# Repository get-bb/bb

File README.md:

<p align="center">
  <picture>
    <source media="(prefers-color-scheme: dark)" srcset="https://github.com/user-attachments/assets/e40bda56-54a4-47f8-a417-6bbadf2e5b40">
    <source media="(prefers-color-scheme: light)" srcset="https://github.com/user-attachments/assets/4d9d02fb-c179-449b-a38a-041955143232">
    
  </picture>
</p>

# bb

bb is an agentic IDE that builds itself. It can control, customize, and automate
itself, laying the groundwork for your own software factory.

Every surface — the desktop app, web app, CLI, and HTTP API — is a first-class
way to drive bb. Work runs in threads you can follow live, steer at any point,
or hand off to another agent.

> [!NOTE]
> bb is in active development. Core architecture is stable, but workflows
> and surfaces are still evolving.

## Use bb

### Download the desktop app

The recommended way to start using bb is the desktop app:

**[Download the latest desktop app](https://github.com/get-bb/bb/releases/tag/desktop-latest)**

The desktop app supports macOS on Apple Silicon (arm64). The Linux x64 AppImage
and the Windows x64 installer are alpha: expect problems, and please report
them. Intel Mac users should run bb with `npx` instead. Native Windows needs
[Git for Windows](https://git-scm.com/download/win), which bb uses for Git and
for environment setup scripts. You can also run bb inside
[WSL2 (Windows Subsystem for Linux)](https://learn.microsoft.com/windows/wsl/install):
install WSL2 first, then run the `npx` command below from your WSL2 (Linux)
shell.

Early adopters can install
**[bb Nightly](https://github.com/get-bb/bb/releases/tag/desktop-nightly)**
alongside the stable desktop app. It has a separate application identity,
yellow icon, and auto-update feed.

### Or run it anywhere with npx

```bash
npx bb-app@latest
```

Then open `http://localhost:38886`.

To control bb from outside bb with the `bb` CLI, open **Settings → General →
Command line** and choose **Install**. See
[The bb Command On PATH](./docs/configuration.md#the-bb-command-on-path).

To run the newest automated build instead:

```bash
npx bb-app@nightly
```

npm 12 and later block dependency install scripts by default. bb needs those
scripts to build its native add-ons. If your npm version is 12 or later, allow
the scripts for the install:

```bash
npx --allow-scripts=better-sqlite3,node-pty,@parcel/watcher bb-app@latest
```

Or set the policy once for all global installs:

```bash
npm config set allow-scripts=better-sqlite3,node-pty,@parcel/watcher --location=user
```

bb uses the provider CLI you already have authenticated.

For install requirements, provider setup, configuration, and package-focused
docs, start with
[`packages/bb-app`](./packages/bb-app/README.md).

### Telemetry

Some new installs try a new version of a feature before everyone else, chosen at random on your device; their events note which version that install has.

Production runs (the desktop app, `npx bb-app`, and `pnpm start` checkouts) send
anonymous usage telemetry (app starts, thread creation counts, user message
counts, and plugin installs) to help us understand adoption. Each event carries
the app version, how bb was installed (desktop, npm, or source checkout), and
the OS release, CPU architecture, and Node version. Source checkouts report whether
`origin` points to `github.com/get-bb/bb`, another repository, or is unavailable.
Telemetry never includes Git commit hashes or remote URLs. Identification is a random per-install
id stored in your data dir — no user, host, project, workspace, or message
content is ever attached. Plugin install events name only public plugins
(bundled plugins and `bb-community` marketplace entries); installs from a local
path, a private git or npm source, or a third-party marketplace report no name. Development runs (`pnpm dev`, `pnpm start:worktree`) never send. Opt out any run with
`BB_TELEMETRY=false`. See
[`apps/server/src/services/system/telemetry.ts`](./apps/server/src/services/system/telemetry.ts).

## Development

Use the development loop when working on bb itself:

```bash
pnpm dev
```

That starts the Vite app and proxies API and WebSocket traffic to a separate
dev server. The launcher prints the actual ports at startup. Each checkout gets
a data directory under
`~/.bb-dev/<checkout-instance>/` and deterministic high ports derived from the
checkout path. The checkout instance id is the sanitized path to the checkout,
relative to your home directory, plus a short hash suffix. Separate worktrees
can run alongside each other and the packaged `npx bb-app@latest` instance.

To test the production bundle and serving path without switching to production
data or ports, use:

```bash
pnpm start:worktree
```

This builds the same optimized frontend and runtime artifacts as `pnpm start`,
then serves the app from the BB server on the checkout-specific dev server port.
It keeps the normal checkout-specific dev data directory and host-daemon port.
There is no Vite dev server or hot reload in this mode; rerun the command after
source changes. As with `pnpm dev`, worktree starts do not send telemetry.

For the Electron desktop shell, keep `pnpm dev` running and start the desktop
package in a second terminal:

```bash
pnpm exec turbo run dev --filter=@bb/desktop
```

The desktop shell connects to this checkout's running dev app. Stop each command
with Ctrl-C in its terminal.

To use the dev app from another machine over Tailscale, start it with the
Tailscale browser origin configured:

```bash
BB_APP_URL=https://<machine>.<tailnet>.ts.net pnpm dev
```

Note the printed app port, then publish the loopback Vite listener in another
terminal:

```bash
tailscale serve --bg --https=443 http://127.0.0.1:<app-port>
```

Then open `https://<machine>.<tailnet>.ts.net`. Source dev binds both the Vite
app and main server to loopback by default; Vite continues to proxy API and
WebSocket traffic.

For direct access at `http://<tailscale-ip>:<app-port>` instead, run:

```bash
pnpm dev:remote
```

This binds the Vite app and main server to all IPv4 interfaces. The remote
browser must be able to reach both the printed app and server ports for realtime
updates. The server API is unauthenticated and permits command execution and
file reads, so use this only behind a trusted network boundary and restrict the
ports to Tailscale traffic with the host firewall when the LAN is not trusted.

To access the production-style worktree server directly from another machine,
run:

```bash
pnpm start:worktree-remote
```

This uses the same checkout-specific data directory and ports as
`pnpm start:worktree`, but binds its single server listener to all IPv4
interfaces. The server API is unauthenticated and permits command execution and
file reads, so use it only behind a trusted network boundary and restrict the
port to Tailscale traffic with the host firewall when the LAN is not trusted.

To use the component storybook from another machine, run:

```bash
pnpm storybook
```

Ladle binds to all interfaces and configures its HMR WebSocket to use the
browser's current host instead of `localhost`. Do not run `pnpm storybook` on an
untrusted network.

Development behavior is intentionally split:

- the app hot reloads itself
- the server does not hot reload
- the host daemon does not hot reload

When you want the server and host daemon to pick up the latest build output, use:

```bash
pnpm dev:restart
pnpm dev:restart-server
pnpm dev:restart-host-daemon
```

These rebuild first, then restart only the targeted stateful services.

To run a production-mode build from a source checkout:

```bash
pnpm start
```

That builds only the app, server, and host-daemon runtime artifacts, then runs
the launcher directly against those workspace outputs. Use the `bb-app`
tarball smoke task when validating the published `npx bb-app@latest` package
layout.

```bash
pnpm bb --help            # built CLI, targets the default/prod instance
pnpm reset                # clear production state

pnpm bb:dev --help        # source CLI, targets this checkout's dev instance
pnpm reset:dev            # clear this checkout's dev state

pnpm reset:all            # clear both production and dev states
```

These reset commands prompt for confirmation before deleting anything.

## Repository Overview

See [Repository overview](docs/repository-overview.md) for the monorepo package and app map.

## System Overview

See [System overview](docs/system-overview.md) for runtime architecture, data model, and component boundaries.

## Further Reading

- [Vision](docs/VISION.md)
- [Platform support](docs/platform-support.md)
- [Configuration](docs/configuration.md)
- [Using bb on multiple devices](docs/multiple-devices.md)
- [Worktrees and setup scripts](docs/worktrees.md)

## Contributing

See [CONTRIBUTING.md](CONTRIBUTING.md) for contribution guidelines.

## Troubleshooting

### `Could not locate the bindings file`

bb uses native add-ons, for example `better-sqlite3` and `@parcel/watcher`. npm
downloads or builds those binaries in a package install script. If npm does not
run install scripts, the binaries are absent. bb then stops at startup with this
error:

```
Error: Could not locate the bindings file. Tried:
 → .../node_modules/better-sqlite3/build/better_sqlite3.node
```

There are two usual causes.

The first cause is npm 12 or later. Since npm 12, npm blocks dependency install
scripts by default and prints
`npm warn install-scripts N packages had install scripts blocked`. Name bb's
native add-ons in `--allow-scripts` to let this one command run their install
scripts:

```bash
npx --allow-scripts=better-sqlite3,node-pty,@parcel/watcher bb-app@latest
```

For a permanent install with the same setting, use:

```bash
npm install -g --allow-scripts=better-sqlite3,node-pty,@parcel/watcher bb-app
bb-app
```

To allow them for all global installs on this machine, run
`npm config set allow-scripts=better-sqlite3,node-pty,@parcel/watcher --location=user`.
npm 10 and 11 accept or ignore the flag, so it is safe on every supported Node.

The second cause is `ignore-scripts=true` in your `~/.npmrc`. Set the
`npm_config_ignore_scripts` environment variable to let this one command run its
install scripts:

```bash
npm_config_ignore_scripts=false npx bb-app@latest
```

For a permanent install with the same setting, use:

```bash
npm_config_ignore_scripts=false npm install -g bb-app
bb-app
```

The environment variable applies to that one command only. Keep
`ignore-scripts=true` in your `~/.npmrc` if you want it for security.

The same error has other causes. A Node.js major-version change after the
install causes it. A copy of `node_modules` from a different operating system,
CPU architecture, or libc variant also causes it. To recover, install the
package again, or run `npm rebuild better-sqlite3`.

## Acknowledgements

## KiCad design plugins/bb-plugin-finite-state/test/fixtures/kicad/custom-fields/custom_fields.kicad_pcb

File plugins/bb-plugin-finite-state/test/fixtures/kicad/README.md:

# KiCad sample projects — L9 test fixtures

Real KiCad projects used by the L9 Hardware Design Plane lane (WP-72…WP-81) for
parser, extraction, and overlay tests.

**This directory is NOT part of the frozen fixture tree.** The freeze covers
`test/mock-remote/fixtures/**` only. L9 owns this directory.

## What belongs here

One subdirectory per project, containing the files as KiCad saves them:

```
test/fixtures/kicad/<project-name>/
  <name>.kicad_pro        # required — discovery keys off this
  <name>.kicad_sch        # required — root sheet (plus any hierarchical sheets)
  <name>.kicad_pcb        # optional — enables board/fab test coverage
```

Requirements for a useful fixture:

- **KiCad 7 or newer** (S-expression format with embedded `lib_symbols`).
  KiCad 5 files are out of scope by spec (SPEC 07 §9).
- At least one multi-unit symbol (e.g. an op-amp: U3A/U3B) and at least one
  part with an `MPN` custom field, so the join-key and HBOM-ingest paths get
  exercised. Parts with *no* MPN are also valuable — that case must stay legal.
- Small enough to live in git. A few sheets is plenty; do not add a
  production-scale board here.

## What tests may assume

- Parsing (`kicadts`) runs with **no KiCad installed** — CI has no `kicad-cli`.
- Anything requiring `kicad-cli` (SVG/GLB export, gerbers, DRC/ERC) must be
  behind a capability check and skip cleanly when the binary is absent.
  Committed expected-output artifacts, if any, live beside the project in an
  `expected/` subdirectory with a note naming the `kicad-cli` version used.

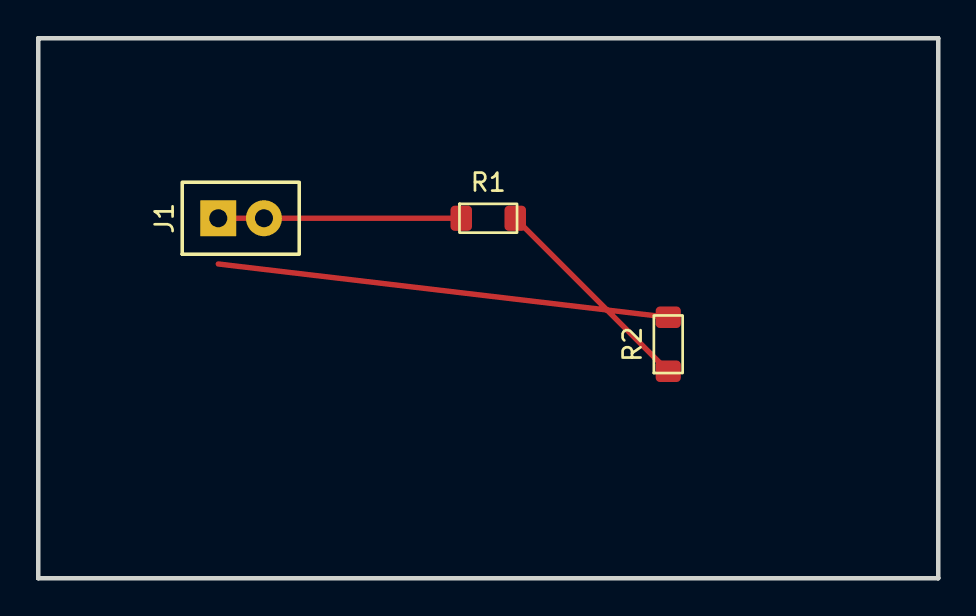
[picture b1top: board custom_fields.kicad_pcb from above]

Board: 2 copper layers, 50.0 x 30.0 mm, 3 parts (0 on the bottom side), 3 nets.

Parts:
J1: CONTROL_IN; Header_1x02
R1: 10k; R_0603
R2: 47k; R_0603

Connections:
CONTROL: R1.2, R2.2
INPUT_SIGNAL: J1.1 (INPUT), R1.1
RETURN_LINK: J1.2 (RETURN), R2.1
